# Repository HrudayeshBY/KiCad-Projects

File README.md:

# KiCad-Projects
I had taken up a course on Udemy titled "PCB design with KiCad" by instructor Dr. Peter Dalmaris. In the course 4 projects were done ranging from beginner to advanced. The project include Simple LED torch, Breadboard Powersupply, Solar power supply and MCU Data Logger in 2 Layer and 4 layer PCB.

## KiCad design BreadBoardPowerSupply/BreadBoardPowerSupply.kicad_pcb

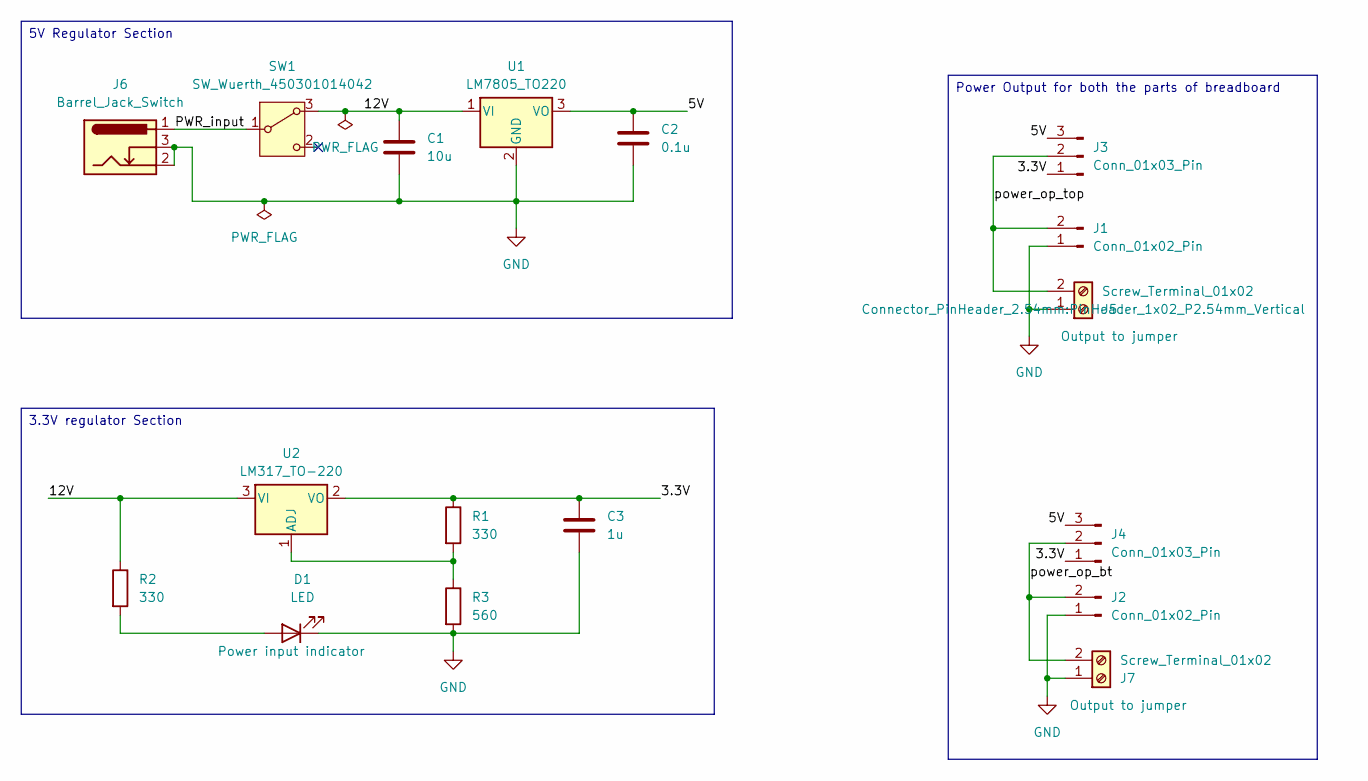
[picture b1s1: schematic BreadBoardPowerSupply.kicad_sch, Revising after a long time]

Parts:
C1: 10u; C_Disc_D3.0mm_W2.0mm_P2.50mm
C2: 0.1u; C_Disc_D3.0mm_W2.0mm_P2.50mm
C3: 1u; C_Disc_D3.0mm_W2.0mm_P2.50mm
D1: LED; LED_D5.0mm
J1, J2: Conn_01x02_Pin; PinHeader_1x02_P2.54mm_Vertical
J3, J4: Conn_01x03_Pin; PinHeader_1x03_P2.54mm_Vertical
J5, J7: Screw_Terminal_01x02; PinHeader_1x02_P2.54mm_Vertical
J6: Barrel_Jack_Switch; BarrelJack_Horizontal
R1, R2: 330; R_Axial_DIN0204_L3.6mm_D1.6mm_P7.62mm_Horizontal
R3: 560; R_Axial_DIN0204_L3.6mm_D1.6mm_P7.62mm_Horizontal
SW1: SW_Wuerth_450301014042; SW_Slide-03_Wuerth-WS-SLTV_10x2.5x6.4_P2.54mm
U1: LM7805_TO220; TO-220-3_Vertical
U2: LM317_TO-220; TO-220-3_Vertical

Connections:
/3.3V: C3.1, J3.1, J4.1, R1.1, U2.2 (VO)
/5V: C2.1, J3.3, J4.3, U1.3 (VO)
/12V: C1.1, R2.1, SW1.3 (A), U1.1 (VI), U2.3 (VI)
/PWR_input: J6.1, SW1.1 (B)
/power_op_bt: J2.2, J4.2, J7.2
/power_op_top: J1.2, J3.2, J5.2
GND: C1.2, C2.2, C3.2, D1.1 (K), J1.1, J2.1, J5.1, J6.2, J6.3, J7.1, R3.2, U1.2 (GND)
unnamed: D1.2 (A), R2.2
unnamed: R1.2, R3.1, U2.1 (ADJ)

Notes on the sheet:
3.3V regulator Section
Power Output for both the parts of breadboard
5V Regulator Section

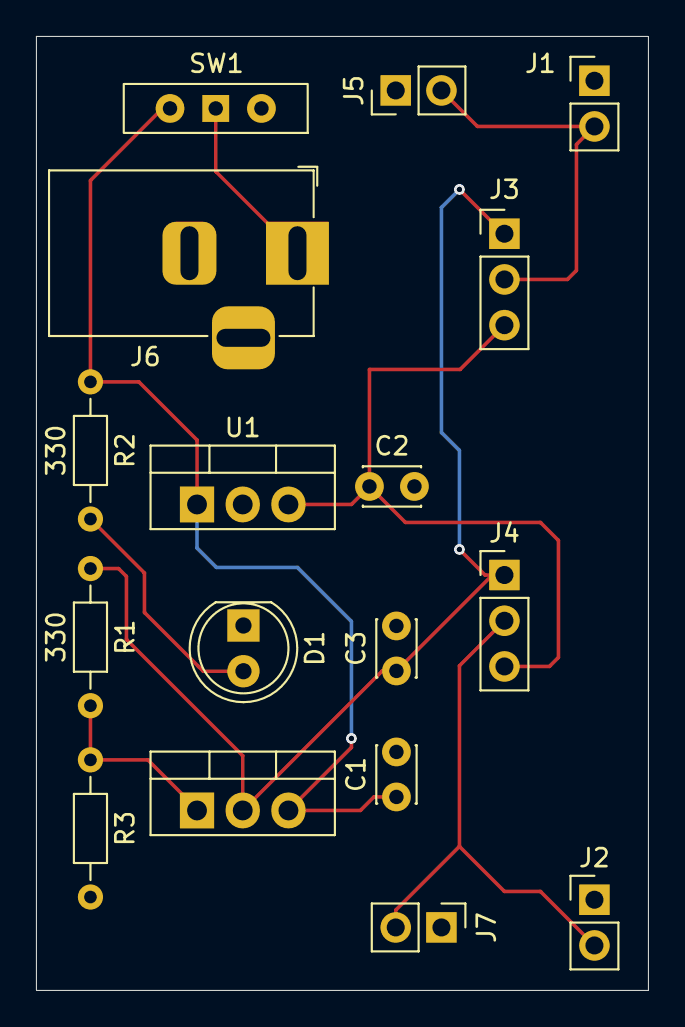
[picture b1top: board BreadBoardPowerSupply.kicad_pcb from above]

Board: 2 copper layers, 34.0 x 53.0 mm, 17 parts (0 on the bottom side), 9 nets.

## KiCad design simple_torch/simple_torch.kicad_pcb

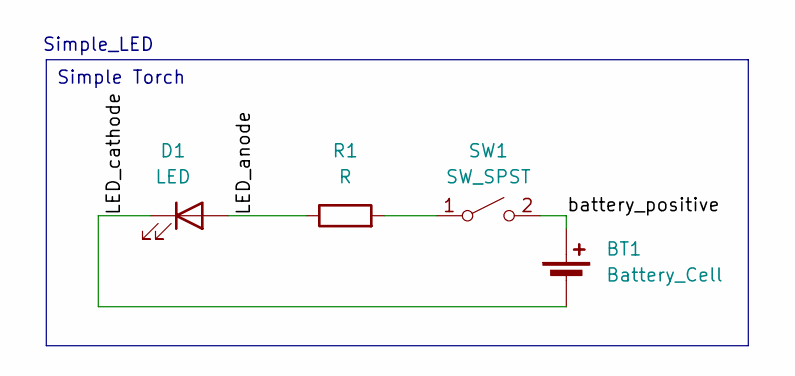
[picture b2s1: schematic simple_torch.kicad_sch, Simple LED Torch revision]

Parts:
BT1: Battery_Cell; BatteryHolder_MYOUNG_BS-07-A1BJ001_CR2032
D1: LED; LED_D3.0mm
R1: R; R_Axial_DIN0204_L3.6mm_D1.6mm_P2.54mm_Vertical
SW1: SW_SPST; SW_TH_Tactile_Omron_B3F-10xx

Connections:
/LED_anode: D1.2 (A), R1.1
/LED_cathode: BT1.2 (-), D1.1 (K)
/battery_positive: BT1.1 (+), SW1.2 (B)
unnamed: R1.2, SW1.1 (A)

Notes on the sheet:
Simple_LED
Simple Torch

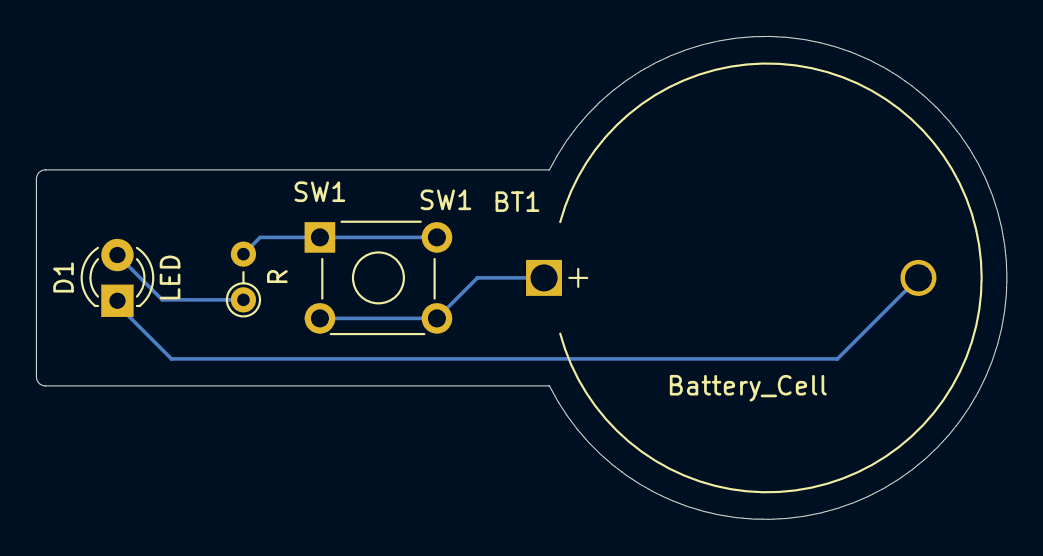
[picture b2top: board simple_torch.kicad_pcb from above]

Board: 2 copper layers, 53.9 x 26.8 mm, 4 parts (0 on the bottom side), 4 nets.

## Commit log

2025-10-05 added all design files
